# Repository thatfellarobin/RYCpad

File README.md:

# RYCpad
[![CC BY-NC-SA 4.0][cc-by-nc-sa-shield]][cc-by-nc-sa]

**RYCpad rendered**

RYCpad (pronounced "ricey pad") is a custom mechanical keyboard numpad with through-hole components. It follows my other project [Axon](https://github.com/thatfellarobin/axon) in its emphasis on symmetric layout. RYCpad runs on an ATmega328P using VUSB and QMK.

RYCpad is designed to be printed with a black substrate PCB and clear solder mask, such as [OSHpark's After Dark service](https://docs.oshpark.com/services/afterdark/). There are no ground planes, allowing the traces to stand out. The plate and bottom PCB have windows in the solder mask to achieve a similar effect without the need for transparent solder mask.

### Resources and Config
The `.svg` file for laser-cutting an acrylic cover for the components can be found in `doc/`. For other materials, a `.dxf` is provided.

The `.svg` file for laser-cutting an acrylic rear plate is also provided in `doc/`. The rear plate is intended to be produced using transparent acrylic, to show off the main PCB. However, a rear plate "PCB" is provided.

A switch plate "PCB" is provided, but a `.dxf` can also be found in `doc/` for those who want to make it from a different material.

⚡⚠️ **Note:** `.svg` files account for a laser kerf of 0.2 mm, but the `.dxf` files do not account for any kerf. `.svg` files use green for cut lines, and blue for engraving.

\
**RYCpad switch plate "PCB"**

The indicator LED is controlled using [QMK's backlight feature](https://github.com/qmk/qmk_firmware/blob/master/docs/feature_backlight.md), which enables hardware PWM dimming in case you find the LED too bright.

### Component Libraries

**Symbols:**
- [Keyboard symbols by Hasu](https://github.com/tmk/kicad_lib_tmk)

**Footprints:**
- [Keyswitches by Daprice](https://github.com/daprice/keyswitches.pretty), but modified for my own tastes/uses.
- My own footprints for mostly decorative things. Can be found in `lib/`

## License
This work is licensed under a
[Creative Commons Attribution-NonCommercial-ShareAlike 4.0 International License][cc-by-nc-sa].

[![CC BY-NC-SA 4.0][cc-by-nc-sa-image]][cc-by-nc-sa]

[cc-by-nc-sa]: http://creativecommons.org/licenses/by-nc-sa/4.0/
[cc-by-nc-sa-image]: https://licensebuttons.net/l/by-nc-sa/4.0/88x31.png
[cc-by-nc-sa-shield]: https://img.shields.io/badge/License-CC%20BY--NC--SA%204.0-lightgrey.svg

If you have built upon this project and have significantly altered the design, the non-commercial clause can be waived with explicit permission.

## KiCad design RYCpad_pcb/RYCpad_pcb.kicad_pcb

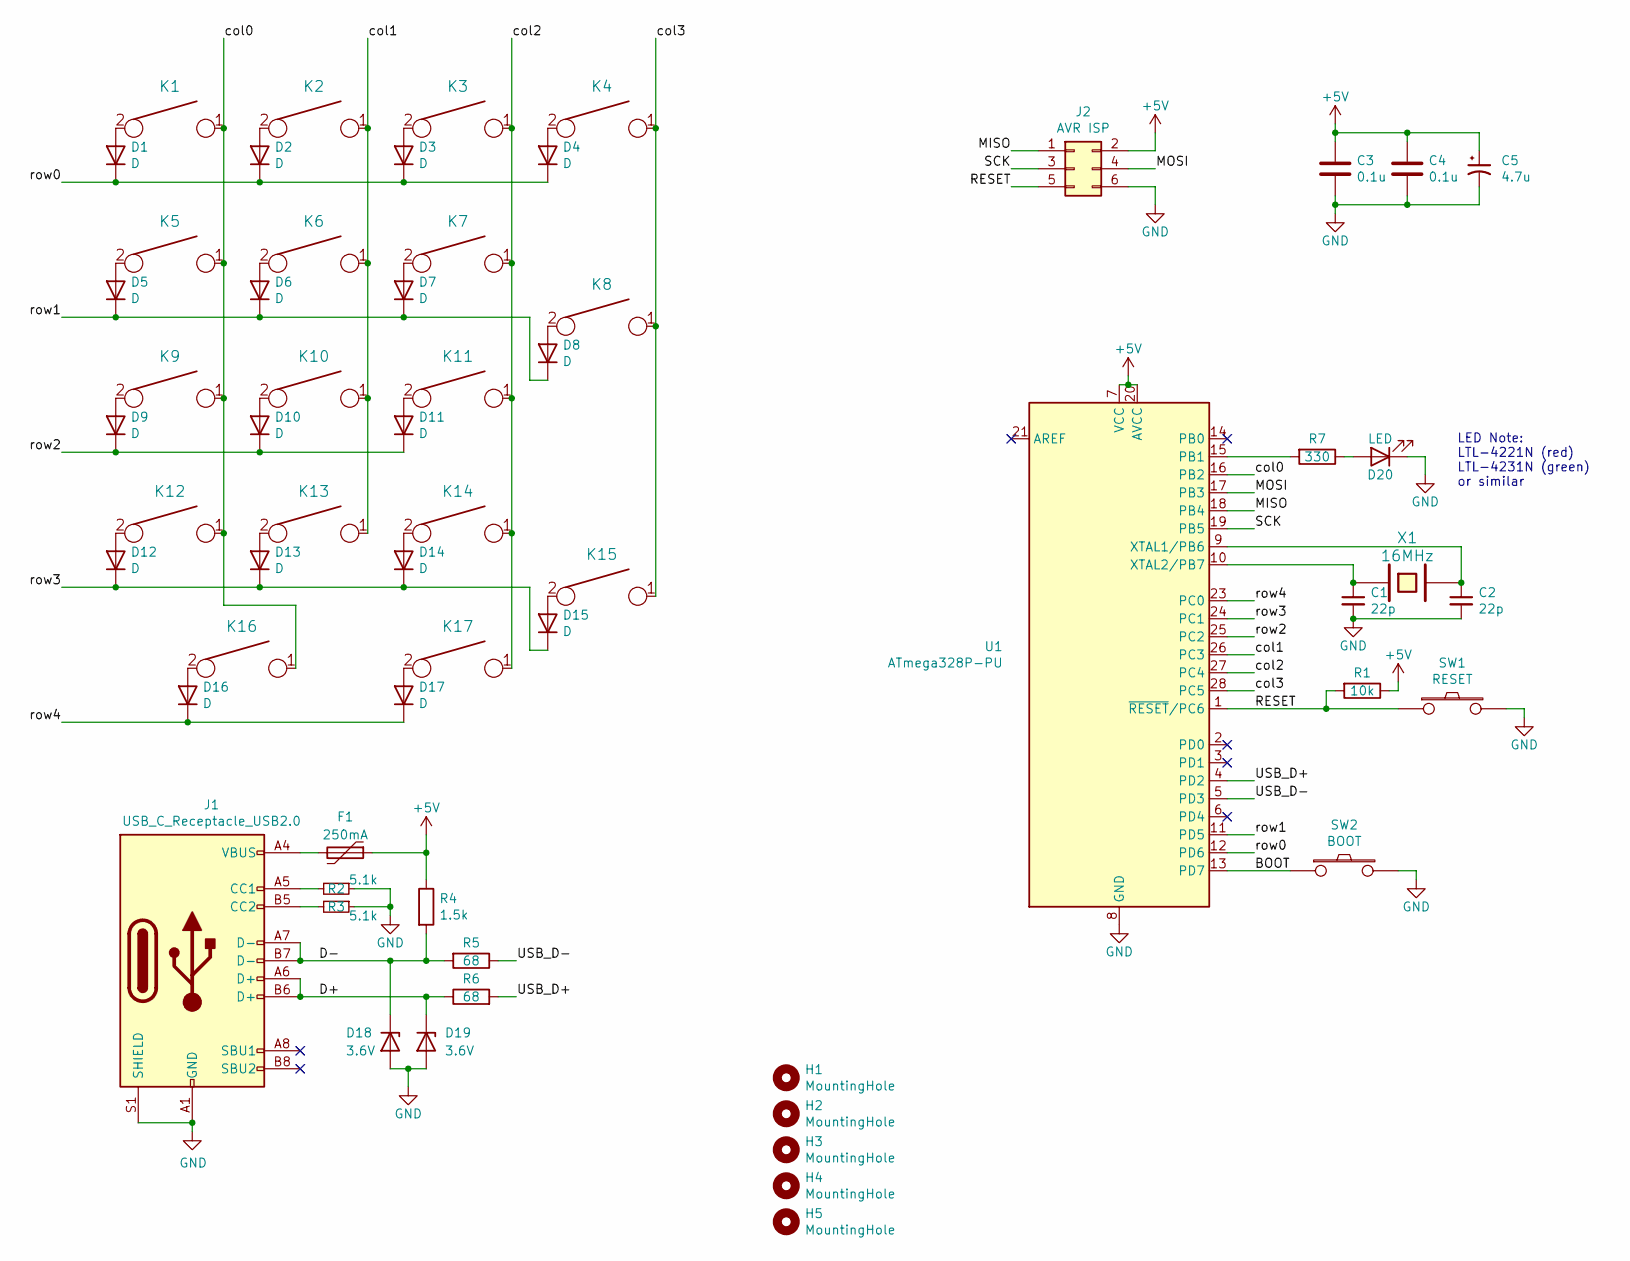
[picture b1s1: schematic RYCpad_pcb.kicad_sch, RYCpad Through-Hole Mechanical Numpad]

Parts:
C1, C2: 22p; C_Disc_D3.0mm_W1.6mm_P2.50mm
C3, C4: 0.1u; C_Disc_D4.3mm_W1.9mm_P5.00mm
C5: 4.7u; CP_Radial_D4.0mm_P1.50mm
D1, D2, D3, D4, D5, D6, D7, D8, D9, D10, D11, D12, D13, D14, D15, D16, D17: D; D_DO-35_SOD27_P5mm_Horizontal
D18, D19: 3.6V; D_DO-35_SOD27_P5mm_Horizontal
D20: LED; LED_D3.0mm
F1: 250mA; C_Disc_D5.0mm_W2.5mm_P5.00mm
H1, H2, H3, H4, H5: MountingHole; MountingHole_2.2mm_M2_Pad
J1: USB_C_Receptacle_USB2.0; USB_C_Receptacle_GCT_USB4085_personalized
J2: AVR ISP; PinHeader_2x03_P2.54mm_Vertical
K1, K2, K3, K4, K5, K6, K7, K8, K9, K10, K11, K12, K13, K14, K15, K16, K17: KEYSW; SW_MX_NoBorderSilk
R1: 10k; R_Axial_DIN0204_L3.6mm_D1.6mm_P5.08mm_Horizontal
R2, R3: 5.1k; R_Axial_DIN0204_L3.6mm_D1.6mm_P5.08mm_Horizontal
R4: 1.5k; R_Axial_DIN0204_L3.6mm_D1.6mm_P5.08mm_Horizontal
R5, R6: 68; R_Axial_DIN0204_L3.6mm_D1.6mm_P5.08mm_Horizontal
R7: 330; R_Axial_DIN0204_L3.6mm_D1.6mm_P5.08mm_Horizontal
SW1: RESET; SW_PUSH_6mm
SW2: BOOT; SW_PUSH_6mm
U1: ATmega328P-PU; DIP-28_W7.62mm
X1: 16MHz; Crystal_HC49-U_Vertical

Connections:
+5V: C3.1, C4.1, C5.1, F1.1, J2.2, R1.1, R4.1, U1.7 (VCC), U1.20 (AVCC)
/BOOT: SW2.1, U1.13 (PD7)
/D+: D19.1 (K), J1.A6 (D+), J1.B6 (D+), R6.1
/D-: D18.1 (K), J1.A7 (D-), J1.B7 (D-), R4.2, R5.2
/MISO: J2.1, U1.18 (PB4)
/MOSI: J2.4, U1.17 (PB3)
/RESET: J2.5, R1.2, SW1.1, U1.1 (~RESET/PC6)
/SCK: J2.3, U1.19 (PB5)
/USB_D+: R6.2, U1.4 (PD2)
/USB_D-: R5.1, U1.5 (PD3)
/col0: K1.1, K5.1, K9.1, K12.1, K16.1, U1.16 (PB2)
/col1: K2.1, K6.1, K10.1, K13.1, U1.26 (PC3)
/col2: K3.1, K7.1, K11.1, K14.1, K17.1, U1.27 (PC4)
/col3: K4.1, K8.1, K15.1, U1.28 (PC5)
/row0: D1.1 (K), D2.1 (K), D3.1 (K), D4.1 (K), U1.12 (PD6)
/row1: D5.1 (K), D6.1 (K), D7.1 (K), D8.1 (K), U1.11 (PD5)
/row2: D9.1 (K), D10.1 (K), D11.1 (K), U1.25 (PC2)
/row3: D12.1 (K), D13.1 (K), D14.1 (K), D15.1 (K), U1.24 (PC1)
/row4: D16.1 (K), D17.1 (K), U1.23 (PC0)
GND: C1.2, C2.2, C3.2, C4.2, C5.2, D18.2 (A), D19.2 (A), D20.1 (K), J1.A1 (GND), J1.A12 (GND), J1.B1 (GND), J1.B12 (GND), J1.S1 (SHIELD), J2.6, R2.1, R3.1, SW1.2, SW2.2, U1.8 (GND), U1.22 (GND)
unnamed: C1.1, U1.10 (XTAL2/PB7), X1.1
unnamed: C2.1, U1.9 (XTAL1/PB6), X1.2
unnamed: D1.2 (A), K1.2
unnamed: D2.2 (A), K2.2
unnamed: D3.2 (A), K3.2
unnamed: D4.2 (A), K4.2
unnamed: D5.2 (A), K5.2
unnamed: D6.2 (A), K6.2
unnamed: D7.2 (A), K7.2
unnamed: D8.2 (A), K8.2
unnamed: D9.2 (A), K9.2
unnamed: D10.2 (A), K10.2
unnamed: D11.2 (A), K11.2
unnamed: D12.2 (A), K12.2
unnamed: D13.2 (A), K13.2
unnamed: D14.2 (A), K14.2
unnamed: D15.2 (A), K15.2
unnamed: D16.2 (A), K16.2
unnamed: D17.2 (A), K17.2
unnamed: D20.2 (A), R7.1
unnamed: F1.2, J1.A4 (VBUS), J1.A9 (VBUS), J1.B4 (VBUS), J1.B9 (VBUS)
unnamed: J1.A5 (CC1), R2.2
unnamed: J1.B5 (CC2), R3.2
unnamed: R7.2, U1.15 (PB1)

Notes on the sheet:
LED Note: LTL-4221N (red) LTL-4231N (green) or similar

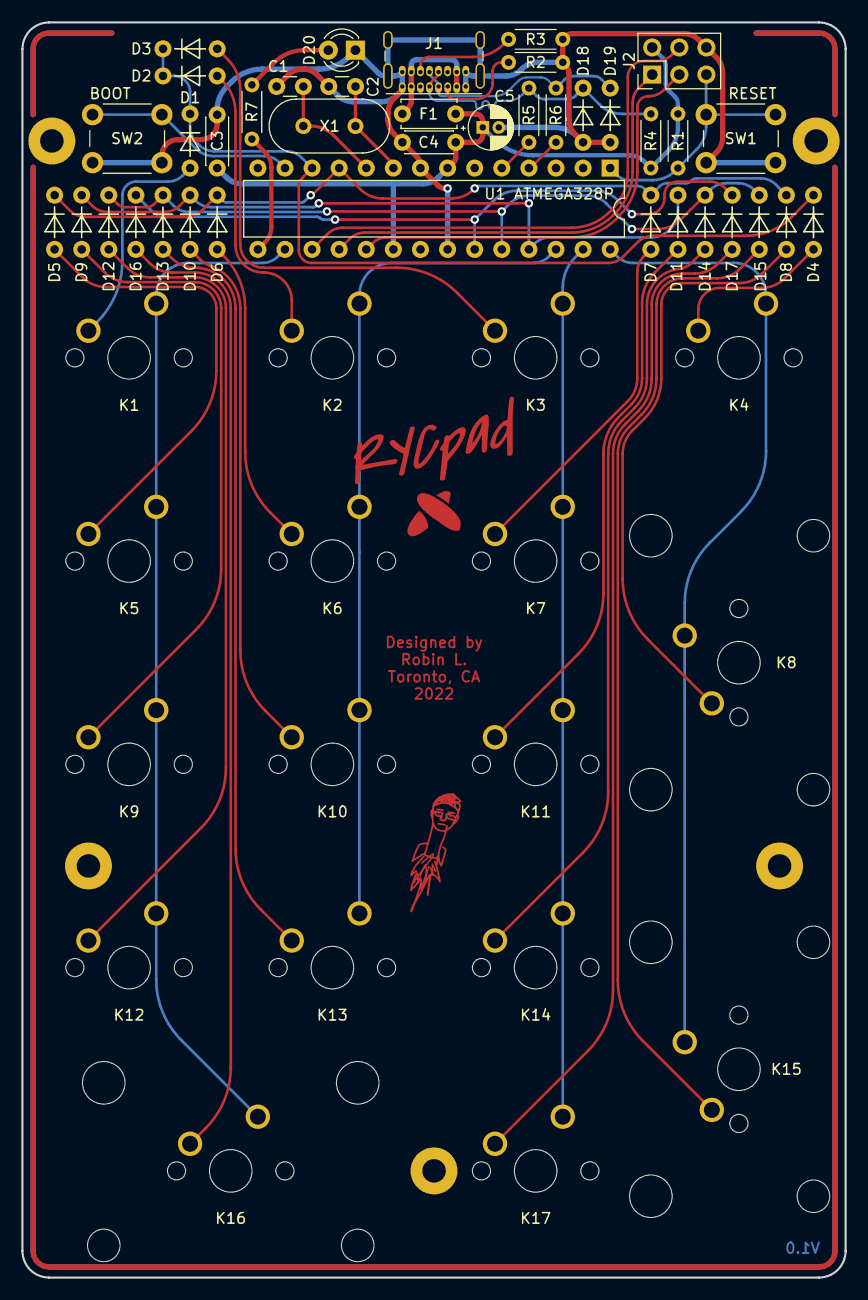
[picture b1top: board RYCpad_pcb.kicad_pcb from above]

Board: 2 copper layers, 77.2 x 117.6 mm, 63 parts (1 on the bottom side), 44 nets.

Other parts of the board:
svg2mod, svg2mod#2: G***; RYCpad_coppertrim_cut

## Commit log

2022-03-11 Rename and fix PCB
    - Renamed files from 'ricey' to RYC
    - Fixed PCB to have all intact connections
2022-03-12 add intended PCB fabrication process to README
2022-03-12 Add logo art
    - also, numerous small routing changes
2022-03-12 update rear pcb
2022-03-12 update license conditions
2022-03-12 minor routing changes
2022-03-12 minor routing changes
    - also, untrack gerbers
2022-03-12 Make LED software-controlled
2022-03-12 add render to readme
2022-03-12 update MCU silkscreen placement
2022-03-12 add rice icon
2022-03-12 rounded all traces
2022-03-12 adjust credits
2022-03-12 add component cover cutpath dxf
2022-03-12 add laser cut outline to PCB file
    - also, a note in the readme regarding laser kerf
2022-03-13 added copper trim
2022-03-13 add version number to pcb
2022-03-14 connected shield through RC filter
2022-03-14 thickened power traces
2022-03-14 aesthetic changes
    - Changed diode footprint to use prettier diode symbol
    - Minor layout adjustments
    - render update to follow in later commit
2022-03-15 new render
    - also, minor routing changes
2022-03-17 minor changes
    - update rear pcb
    - thinner silkscreen lines on diode footprint
2022-03-18 USB dataline symmetry
2022-03-20 add plate file
2022-03-20 matched USB data line length
2022-03-20 revise usb shield strategy
    - now shorted to ground
2022-03-20 ground trace thickness fix
2022-03-21 update rear pcb
    - Add solder mask windows to allow copper to show even at cheaper board
    shops
    - Add copper trim around the edge of the rear pcb
2022-03-21 add pcb plate
2022-03-21 routing improvements
    - render to follow
2022-03-21 update copper trim
2022-03-22 minor routing changes, add suggested led
2022-03-22 add candidate gerber for 1.0 final
2022-03-23 update plate "PCB" and produce gerber
2022-03-23 update LED pin
    - QMK supports hardware PWM on pin PB1 and PB2 for backlight dimming.
    The hope is that hardware PWM dimming can be exploited for the
    indicator LED, which mitigates any issues related to excessive LED
    brightness.
2022-03-23 adjust col1 pin
    change col1 pin PB3 >>> PC3
2022-03-23 update readme and render
2022-03-24 add copper pour to plate
2022-03-24 change LED resistor default value
2022-03-24 added more decoration to plate
2022-03-24 readme formatting fix
2022-03-25 adjusted component cover and plate
    - Old plate geometry would collide with IC socket
    - Component cover lower edge pushed to show bottom edges of components
    more clearly
    - Plate upper edge pushed to eliminate collision with IC socket
2022-03-25 re-export gerber
2022-04-03 add rear plate cutfile
2022-04-03 add component cover svg
2022-04-03 readme adjustment
